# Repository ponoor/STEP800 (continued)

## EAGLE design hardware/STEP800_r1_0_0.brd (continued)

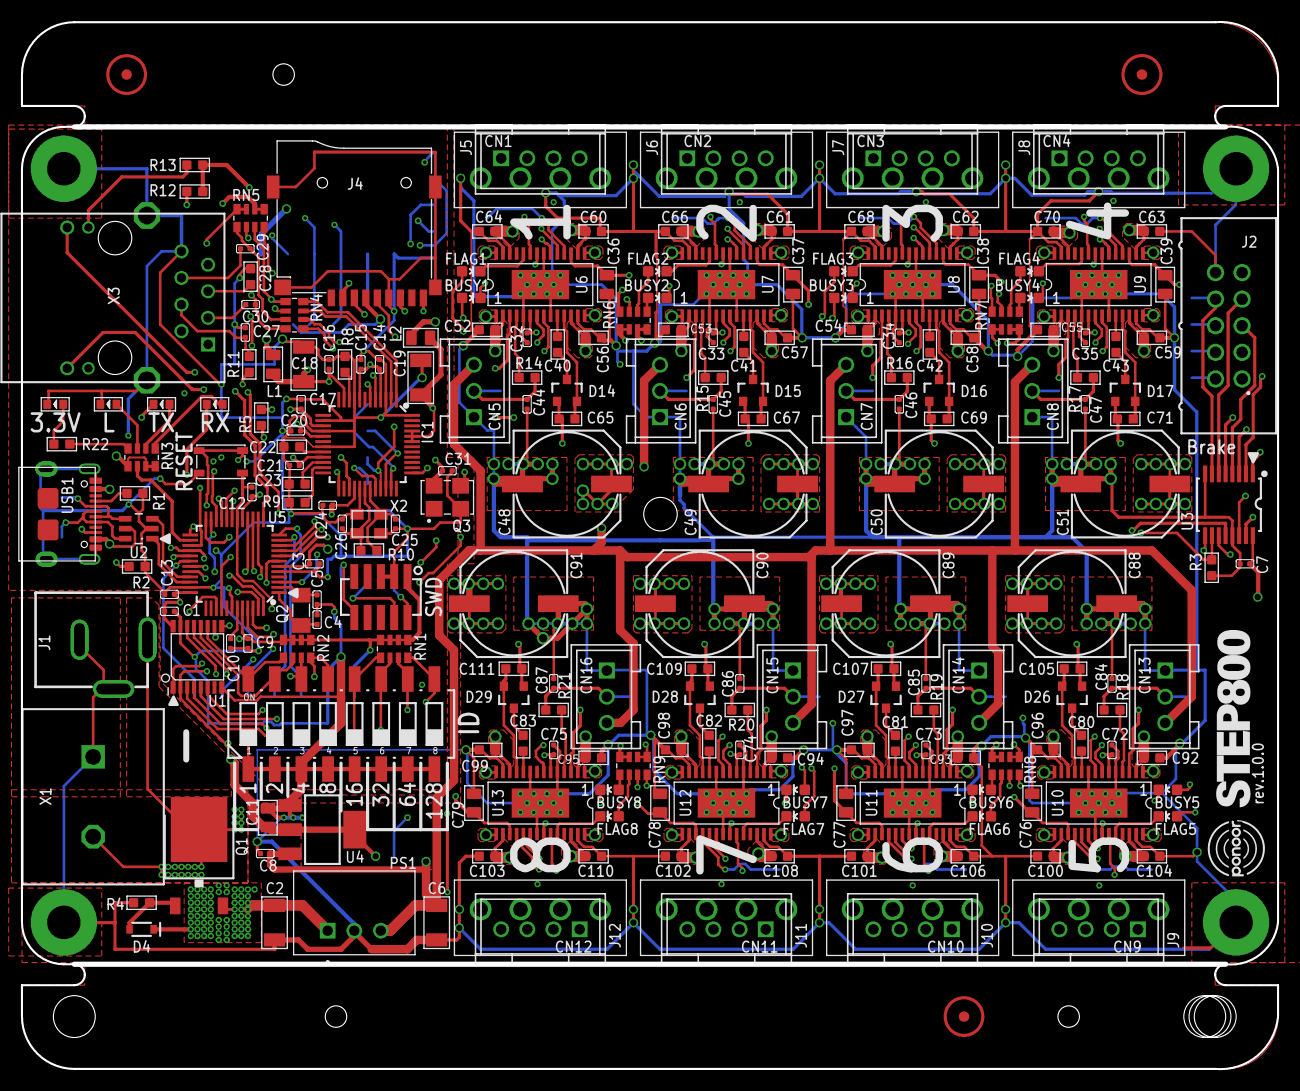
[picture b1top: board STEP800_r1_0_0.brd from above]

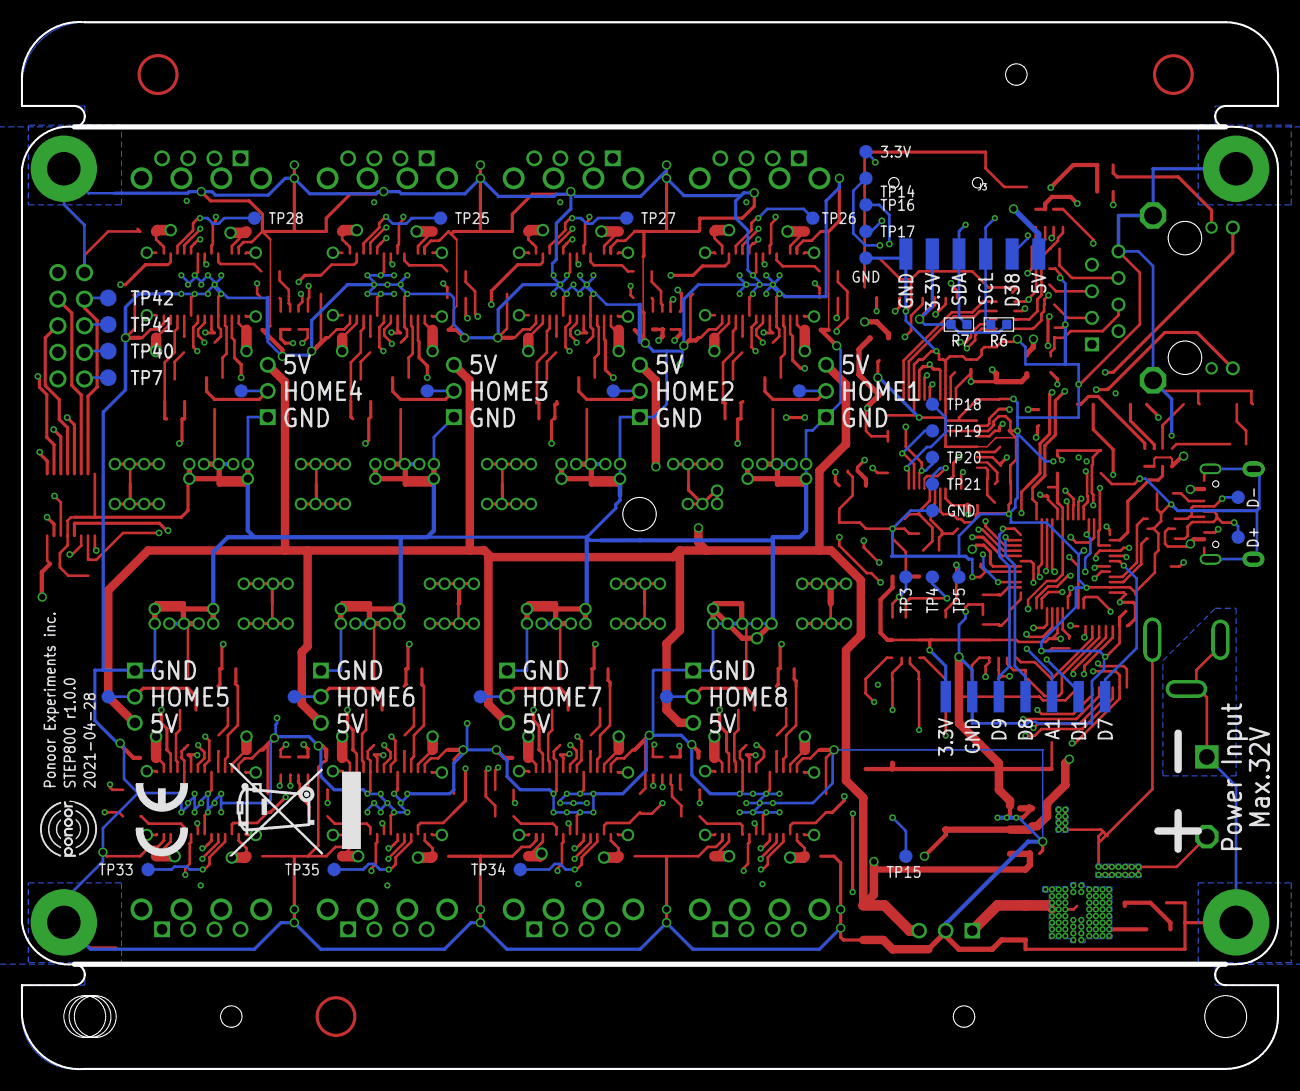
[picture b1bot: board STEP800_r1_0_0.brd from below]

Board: 4 copper layers, 120.0 x 100.0 mm, 280 parts (48 on the bottom side), 219 nets.

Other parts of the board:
U$1: WEEE_13MM
U$2: STEP800_LOGO_L_16MM
U$3: CE_5MM
U$4, U$5: PONOOR_LOGO_6MM

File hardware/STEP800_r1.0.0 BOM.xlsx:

# | Name | Value | Description | Package | Manufacture | MPN | Qty | Parts | Type
1.0 | SMD-LED | GREEN | Various green LEDs | LED-0603 | Everlight Elec | 19-213/GHC-YR1S2M/3T | 9.0 | 3.3V, BUSY1, BUSY2, BUSY3, BUSY4, BUSY5, BUSY6, BUSY7, BUSY8 | SMT
2.0 | MLCC | 100nF / 25V | 100nF / 20% / 25V / X5R | C0402 | Walsin Tech Corp | 0402X104K160CT | 32.0 | C1, C3, C7, C8, C9, C10, C12, C13, C14, C15, C16, C17, C20, C21, C24, C31, C32,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 | SMT
3.0 | MLCC | 10uF/10V | 10uF / 20% / 10V / X5R | C0805 | Samsung Electro-Mechanics | CL21A106KOQNNNG | 9.0 | C11, C36, C37, C38, C39, C76, C77, C78, C79 | SMT
4.0 | MLCC | 47uF/6.3V | 47uF / 20% / 6.3V / X5R | C1206 | Samsung Electro-Mechanics | CL31A476MQHNNWE | 2.0 | C18, C19 | SMT
5.0 | MLCC | 10uF/50V | 10uF / 20% / 50V / X5R | C1206 | Samsung Electro-Mechanics | CL31A106KBHNNNE | 2.0 | C2, C6 | SMT
6.0 | MLCC | 4.7uF / 6.3V | 4.7uF / 20% / 6.3V / X5R | C0603 | Samsung Electro-Mechanics | CL10A475KQ8NNNC | 1.0 | C22 | SMT
7.0 | MLCC | 10nF/50V | 10nF / 20% / 50V / X5R | C0603 | Samsung Electro-Mechanics | CL10B103KB8NNNC | 10.0 | C23, C28, C40, C41, C42, C43, C80, C81, C82, C83 | SMT
8.0 | MLCC | 22nF 50V | 22nF / 20% / 50V / X5R | C0402 | Walsin Tech Corp | 0402F223Z500CT | 1.0 | C27 | SMT
9.0 | MLCC | 6.8nF/25V | 6.8nF / 20% / 25V / X5R | C0402 | Walsin Tech Corp | 0402B682K500CT | 2.0 | C29, C30 | SMT
10.0 | MLCC | 22pF/50V | 22pF / 10% / 50V / X5R | C0402 | Walsin Tech Corp | 0402N220J500 | 4.0 | C4, C5, C25, C26 | SMT
11.0 | MLCC | 220nF / 25V | 220nF / 20% / 25V / X5R | C0603 | Samsung Electro-Mechanics | CL10F224ZA8NNNC | 8.0 | C65, C67, C69, C71, C105, C107, C109, C111 | SMT
12.0 | Chemical Capacitor | 220uF / 50V | 220uF ±20% 50V 10mm | SMD,10x10mm | Rubycon | 50TLV220M10X10.5 | 8.0 | C48, C49, C50, C51, C88, C89, C90, C91 | SMT
13.0 | MLCC | 100nF/50V | 100nF / 20% / 50V / X5R | C0603 | Walsin Tech Corp | 0603B104K500CT | 32.0 | C52, C53, C54, C55, C56, C57, C58, C59, C60, C61, C62, C63, C64, C66, C68, C70,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 | SMT
14.0 | Shrouded header | 2.5mm, 4P | B4B-XASK-1 | B4B-XASK-1 | JST | B04B-XASK-1(LF)(SN) | 8.0 | CN1, CN2, CN3, CN4, CN9, CN10, CN11, CN12 |  | NO MOUNT
15.0 | Shrouded header | 2.5mm, 3P | B3B-XASK-1 | B3B-XASK-1 | JST | B03B-XASK-1(LF)(SN) | 8.0 | CN5, CN6, CN7, CN8, CN13, CN14, CN15, CN16 | THT
16.0 | Switching diode array | BAV99 | Series-pair diode array | SOT23-3 | Nexperia | BAV99,215 | 8.0 | D14, D15, D16, D17, D26, D27, D28, D29 | SMT
17.0 | Zener Diode | 5.6V, 300mW | 5.6V ±7% 300mW | SOD-323 | ON Semiconductor | MM3Z5V6T1G | 1.0 | D4 | SMT
18.0 | SMD-LED | Red | general LED red | LED-0603 | Lite-On | LTST-C193KRKT-5A | 9.0 | FLAG1, FLAG2, FLAG3, FLAG4, FLAG5, FLAG6, FLAG7, FLAG8, TX | SMT
19.0 | Ethernet Controller |  |  | TQFP48 | WIZnet | W5500 | 1.0 | IC1 | SMT
20.0 | DIP Switch |  | 8 digits | 2.54mm pitch SMD | Cixi Tonver Elec | HAD-08HWA-R | 1.0 | ID | SMT
21.0 | DC Power receptacle |  | DC Power Receptacle Jack 5A 2.0mm 6.2mm | POWERJACK_SLOT | XKB Connectivity | DC-005-5A-2.0 | 1.0 | J1 | THT
22.0 | Box header |  | Header 10P 0.100"(2.54mm) 2 | 6.1201021621E10 | BOOMELE(Boom Precision Elec) | C5665 | 1.0 | J2 | THT
23.0 | Micro SD card slot |  |  |  | XUNPU | TF-115K | 1.0 | J4 | SMT
24.0 | 3.81mm 4pin header |  |  |  | Ningbo Kangnex Elec | WJ15EDGVC-3.81-4P | 8.0 | J5, J6, J7, J8, J9, J10, J11, J12 | THT
25.0 | SMD-LED | Orange | general LED orange | LED-0603 | Lite-On | LTST-C191KFKT | 1.0 | L | SMT
26.0 | Ferrite Beads | 330R-1500MA | 330Ω @ 100MHz 1.5A | L0805 | Murata Electronics | BLM21PG331SN1D | 2.0 | L1, L2 | SMT
27.0 | DC-DC Converter | P78E05-1000 | 9-36V input, 5V output, 1000mA | CONV_P78E05-1000 | CUI Inc. | P78E05-1000 | 1.0 | PS1 | THT
28.0 | P-MOSFET |  | 100V 46A | D-PAK(TO252AA) | Winsok Semicon | WSF45P10 | 1.0 | Q1 | SMT
29.0 | Crystal Resonators | 32.768kHz | CRYSTAL | SMD-3215_2P | EPSON | FC-135 32.7680KA-A0 | 1.0 | Q2 | SMT
30.0 | Crystal Oscillator |  | 16MHz ±100ppm 3.3V | SG5032 | Seiko Epson | X1G004451000200 | 1.0 | Q3 | SMT
31.0 | Chip Resistor | 5.1k | ±0.5% 0.1W | R0603 | YAGEO | RC0603DR-075K1L | 2.0 | R1, R2 | SMT
32.0 | Chip Resistor | 1M 1/10W | 5% 1/10W | R0603 | YAGEO | AC0603JR-071ML | 1.0 | R10 | SMT
33.0 | Chip Resistor | 10R | 5% 1/10W | R0603 | YAGEO | RC0603JR-0710RL | 1.0 | R11 | SMT
34.0 | Chip Resistor | 330R | 5% 1/10W | R0603 | YAGEO | RC0603JR-07330RL | 3.0 | R12, R13, R22 | SMT
35.0 | Chip Resistor | 100R | 5% 1/10W | R0603 | YAGEO | RC0603JR-07100RL | 8.0 | R14, R15, R16, R17, R18, R19, R20, R21 | SMT
36.0 | Chip Resistor | 100k | 5% 1/10W | R0603 | YAGEO | RC0603JR-07100KL | 4.0 | R3, R4, R5, R9 | SMT
37.0 | Chip Resistor | 12.4K | 1％ 1/10W | R0603 | YAGEO | AC0603FR-0712K4L | 1.0 | R8 | SMT
38.0 | Tactile Switch |  | SWITCH-SPST | 4.6x3.2 | ALPS Electric | SKRPABE010 | 1.0 | RESET | SMT
39.0 | Array Chip Resistor | 100k | 5% 1/16W | R0603 x4 | Bourns | CAY16-104J4LF | 2.0 | RN1, RN2 | SMT
40.0 | Array Chip Resistor | 330.0 | 5% 1/16W | R0603 x4 | Bourns | CAY16-331J4LF | 5.0 | RN3, RN6, RN7, RN8, RN9 | SMT
41.0 | Array Chip Resistor | 33.0 | 5% 1/16W | R0603 x4 | Bourns | CAY16-330J4LF | 1.0 | RN4 | SMT
42.0 | Array Chip Resistor | 49.9 | 1% 1/16W | R0603 x4 | Bourns | CAY16-49R9F4LF | 1.0 | RN5 | SMT
43.0 | SMD-LED | Yellow | general LED yellow | LED-0603 | Lite-On | LTST-C191KSKT | 1.0 | RX | SMT
44.0 | Pin Header | 10 pin | Cortex Debug Connector | 1.27mm Pin Header 10P | Amphenol ICC | 20021121-00010C4LF | 1.0 | SWD | SMT
45.0 | Logic IC | 74HC165PW | 8-bit parallel-in/serial out shift register | TSSOP16 | Nexperia | 74HC165PW,118 | 1.0 | U1 | SMT
46.0 | TVS Diode Array | USBLC6-2SC6 | STMicroelectronics USBLC6 | SOT23-6L | STMicroelectronics | USBLC6-2SC6 | 1.0 | U2 | SMT
47.0 | Logic IC | 74HC595 | 8-Bit Shift Register (Serial to Parallel) | TSSOP16 | Nexperia | 74HC595PW,118 | 1.0 | U3 | SMT
48.0 | Voltage Regulator | LD1117S33 | 3.3V 0.8A | SOT223 | STMicroelectronics | LD1117S33TR | 1.0 | U4 | SMT
49.0 | MCU |  |  | TQFP-48 | Microchip | ATSAMD21G18A-AU | 1.0 | U5 | SMT
50.0 | Stepper Driver IC |  |  | HTSSOP28 | STMicroelectronics | L6470H | 8.0 | U6, U7, U8, U9, U10, U11, U12, U13 | SMT
51.0 | USB Type C Connector |  | USB - Type C Female 16 SMT | USB-C_USB2.0-TYPE-C | XKB Connectivity | U262-161N-4BVC11 | 1.0 | USB1 | THT
52.0 | Barrier Terminal Block | 7.62mm, 2P |  | 7.62mm | Ningbo Kangnex Elec | WJ25C-B-7.62-2P | 1.0 | X1 | THT
53.0 | Crystal Resonators | 25MHz | 25MHz ±20ppm12pF | CRYSTAL-3225 | Seiko Epson | X1E000021013900 | 1.0 | X2 | SMT
54.0 | RJ45 Jack with Magnetics |  |  |  | Hanrun | HR871181A | 1.0 | X3 | THT

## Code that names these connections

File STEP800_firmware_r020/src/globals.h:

// globals.h

#ifndef _GLOBALS_h
#define _GLOBALS_h

#if defined(ARDUINO) && ARDUINO >= 100
	#include "arduino.h"
#else
	#include "WProgram.h"
#endif
#include <SPI.h>
#include <Ponoor_L6470Library.h>
#include <Ethernet.h>

// =============================================================================
// Board / Pin definitions
// =============================================================================
// #define PROTOTYPE_BLACK // First Black PCB prototype
//#define PROTOTYPE_R3 // Uncomment this line for the prototype r4 pcb.
// r3: revision anno lab 2020
// r4: with brake connector 2021 (production ver)


#ifdef PROTOTYPE_R3 // ----------------- Prototype r3 -----------------
    #define HAS_SD
    #define ledPin	13u
    // L6470
    #define L6470_MISO	6	// D6 /SERCOM3/PAD[2] miso
    #define L6470_MOSI	11	// D11/SERCOM3/PAD[0] mosi
    #define L6470_SCK	12	// D12/SERCOM3/PAD[3] sck

    #define L6470_CS_PIN A0
    #define L6470_RESET_PIN A2
    // Shift registers
    // 74HC165 shift register for dip switch and busy/flag input
    #define MISO3	3 // SERCOM2/PAD[1]
    #define MOSI3   2 // SERCOM2/PAD[2] // not in use
    #define SCK3	0 // SERCOM2/PAD[3]
    #define LATCH3	A5
    // Shift registers SPI
    extern SPIClass SPI3;

    // W5500
    #define W5500_RESET_PIN A3

    #define SETUP_SW_PIN	5u
#elif defined(PROTOTYPE_BLACK) // ----------------- Prototype D_L6470x8_black -----------------
    #define ledPin	4u
    // L6470
    #define L6470_MISO	12	// 
    #define L6470_MOSI	11	// 
    #define L6470_SCK	13	// 
    #define L6470_CS_PIN 9
    #define L6470_RESET_PIN A5
    // Shift Registers
    #define MISO3   A3
    #define LATCH3  A1
    #define SCK3    A2
    // W5500
    #define W5500_RESET_PIN 8
#else // ----------------- Product version -----------------
    #define HAS_SD
    #define HAS_BRAKE
    #define ledPin	13u
    // L6470
    #define L6470_MISO	6	// D6 /SERCOM3/PAD[2] miso
    #define L6470_MOSI	11	// D11/SERCOM3/PAD[0] mosi
    #define L6470_SCK	12	// D12/SERCOM3/PAD[3] sck

    #define L6470_CS_PIN A0
    #define L6470_RESET_PIN A2
    // Shift registers
    // 74HC165 +74HC595 for the dip sw input and the brake output
    #define MISO3	3 // SERCOM2/PAD[1]
    #define MOSI3   2 // SERCOM2/PAD[2]
    #define SCK3	0 // SERCOM2/PAD[3]
    #define LATCH3	A5
    // Shift registers SPI
    extern SPIClass SPI3;

    // W5500
    #define W5500_RESET_PIN A3

    #define SHIFTOUT_ENABLE_PIN 5u
#endif

// =============================================================================
// Pin definitions
// =============================================================================
#ifdef HAS_SD
#define SD_CS_PIN	4u
#define SD_DETECT_PIN   A4
#endif

// =============================================================================
// Constants and variables
// =============================================================================

// General
#define COMPILE_DATE __DATE__
#define COMPILE_TIME __TIME__
extern const char *firmwareName;
extern const uint8_t firmwareVersion[3]; // defined in the main Arduino sketch
extern int8_t loadedConfigVersion[2];
extern const uint8_t applicableConfigVersion[2];
#define STATUS_POLL_PERIOD   1 // [ms]


// Tx, Rx LED
extern bool rxLedEnabled, txLedEnabled;
extern uint32_t RXL_blinkStartTime, TXL_blinkStartTime;
#define RXL_TXL_BLINK_DURATION	30 // ms

// Json configuration file
constexpr char* filename = "/config.txt";
extern String configName;
extern String configTargetProduct;
extern bool sdInitializeSucceeded;
extern bool configFileOpenSucceeded;
extern bool configFileParseSucceeded;

// L6470
#define NUM_OF_MOTOR   (8)
extern AutoDriver stepper[];
#define MOTOR_ID_ALL    255
#define MOTOR_ID_FIRST  1
#define MOTOR_ID_LAST   8

// Network
extern uint8_t mac[6], mac_from_config[6], myId;
extern IPAddress
    myIp,
    myIp_from_config,
    destIp,
    dns,
    gateway,
    subnet;
const IPAddress broadcastIp(255, 255, 255, 255);
extern unsigned int inPort, outPort, outPort_from_config;
extern EthernetUDP Udp;
extern bool
    isDestIpSet,
    isMyIpAddId,
    isMacAddId,
    isOutPortAddId,
    bootedMsgEnable,
    isWaitingSendBootMsg,
    reportErrors;
#define BOOT_MSG_WAIT_TIME  1000    //[ms], The waiting duration for sending a boot message after Ethernet has been linked

// Motor settings.

// Brake
#ifdef HAS_BRAKE
extern uint8_t brakeOut;
#endif
extern uint8_t brakeStatus[NUM_OF_MOTOR];
enum {
    BRAKE_ENGAGED = 0,
    BRAKE_DISENGAGE_WAITING, // motor excited
    BRAKE_DISENGAGED,
    BRAKE_MOTORHIZ_WAITING // brake closed
};
extern uint32_t brakeTransitionTrigTime[NUM_OF_MOTOR];
extern bool bBrakeDecWaiting[NUM_OF_MOTOR]; // Waiting deceleration for the brake engaging procedure

// Homing
extern uint32_t homingStartTime[NUM_OF_MOTOR];
extern uint8_t homingStatus[NUM_OF_MOTOR];
extern bool bHoming[NUM_OF_MOTOR];
extern float homingSpeed[NUM_OF_MOTOR];
enum {
    HOMING_UNDEFINED = 0,
    HOMING_GOUNTIL,
    HOMING_RELEASESW,
    HOMING_COMPLETED,
    HOMING_TIMEOUT
};

// Command errors
enum {
    ERROR_COMMAND_IGNORED = 0,
    ERROR_MOTORID_NOTMATCH,
    ERROR_BRAKE_ENGAGED,
    ERROR_HOMESW_ACTIVATING,
    //ERROR_LIMITSW_ACTIVATING,
    ERROR_GOUNTIL_TIMEOUT,
    ERROR_RELEASESW_TIMEOUT,
    ERROR_IN_SERVO_MODE
};
const String commandErrorText[8] = {
    F("CommandIgnored"),
    F("MotorIdNotMatch"),
    F("BrakeEngaged"),
    F("HomeSwActivating"),
    //F("LimitSwActivating"),
    F("GoUntilTimeout"),
    F("ReleaseSwTimeout"),
    F("InServoMode")
};
// These values will be initialized at loadConfig()
extern bool
    busy[NUM_OF_MOTOR],
    HiZ[NUM_OF_MOTOR],
    homeSwState[NUM_OF_MOTOR],
    dir[NUM_OF_MOTOR],
    uvloStatus[NUM_OF_MOTOR];
extern uint8_t
    motorStatus[NUM_OF_MOTOR],
    thermalStatus[NUM_OF_MOTOR];

extern bool
    reportBUSY[NUM_OF_MOTOR],
    reportHiZ[NUM_OF_MOTOR],
    reportHomeSwStatus[NUM_OF_MOTOR],
    reportDir[NUM_OF_MOTOR],
    reportMotorStatus[NUM_OF_MOTOR],
    reportSwEvn[NUM_OF_MOTOR],
    reportUVLO[NUM_OF_MOTOR],
    reportThermalStatus[NUM_OF_MOTOR],
    reportOCD[NUM_OF_MOTOR],
    reportStall[NUM_OF_MOTOR],
    //limitSwState[NUM_OF_MOTOR],
    //reportLimitSwStatus[NUM_OF_MOTOR],
    //limitSwMode[NUM_OF_MOTOR],
    homingDirection[NUM_OF_MOTOR],
    bProhibitMotionOnHomeSw[NUM_OF_MOTOR],
    //bProhibitMotionOnLimitSw[NUM_OF_MOTOR],
    bHomingAtStartup[NUM_OF_MOTOR];
extern uint16_t
    goUntilTimeout[NUM_OF_MOTOR],
    releaseSwTimeout[NUM_OF_MOTOR];
extern uint8_t kvalHold[NUM_OF_MOTOR], kvalRun[NUM_OF_MOTOR], kvalAcc[NUM_OF_MOTOR], kvalDec[NUM_OF_MOTOR];
//extern uint8_t tvalHold[NUM_OF_MOTOR], tvalRun[NUM_OF_MOTOR], tvalAcc[NUM_OF_MOTOR], tvalDec[NUM_OF_MOTOR];
//extern bool isCurrentMode[NUM_OF_MOTOR];
extern bool homeSwMode[NUM_OF_MOTOR];

extern uint16_t intersectSpeed[NUM_OF_MOTOR]; // INT_SPEED
extern uint8_t
    startSlope[NUM_OF_MOTOR], // ST_SLP
    accFinalSlope[NUM_OF_MOTOR], // FN_SLP_ACC
    decFinalSlope[NUM_OF_MOTOR], // FN_SLP_DEC
    stallThreshold[NUM_OF_MOTOR]; // STALL_TH
// extern uint8_t
//     fastDecaySetting[NUM_OF_MOTOR], // T_FAST
//     minOnTime[NUM_OF_MOTOR], // TON_MIN
//     minOffTime[NUM_OF_MOTOR]; // TOFF_MIN
extern uint8_t
    overCurrentThreshold[NUM_OF_MOTOR], // OCD
    microStepMode[NUM_OF_MOTOR]; // STEP_MODE
extern uint16_t slewRate[NUM_OF_MOTOR]; // GATECFG1
extern uint8_t slewRateNum[NUM_OF_MOTOR]; // [0]114, [1]220, [2]400, [3]520, [4]790, [5]980.
extern float lowSpeedOptimize[NUM_OF_MOTOR];
extern bool electromagnetBrakeEnable[NUM_OF_MOTOR];
extern uint16_t brakeTransitionDuration[NUM_OF_MOTOR];
extern float
    acc[NUM_OF_MOTOR],
    dec[NUM_OF_MOTOR],
    maxSpeed[NUM_OF_MOTOR],
    fullStepSpeed[NUM_OF_MOTOR];

// Servo mode
extern int32_t targetPosition[NUM_OF_MOTOR];
extern float kP[NUM_OF_MOTOR], kI[NUM_OF_MOTOR], kD[NUM_OF_MOTOR];
extern boolean isServoMode[NUM_OF_MOTOR];
#endif

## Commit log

2021-04-14 Added hardware design files
2021-04-20 Added firmware files
2021-04-23 Added multiple boards support
2021-04-27 Fixed a SPI pin for shift registers
2021-04-28 Fixed loading myIp, outPort and mac when the DIP sw changed.
    And PROTOTYPE_BLACK bugs fix
2021-04-28 Updated the diagnosis outputs
2021-04-28 Updated hardware design files
2021-04-30 Fixed the L6470 reset pin logic state for prototype pcb
2021-05-03 Fixed the wrong parsing when loading integer as bool in the config.txt
2021-05-07 Silk adjustments for the Eagle board design file
2021-05-09 Added the hardware inspection sketch
2021-05-10 Updated the hardware test sketch
2021-05-17 Correct the external OSC frequency for prototype_black
2021-07-12 Rename test_prcedure.md to 1_preparation.md
2021-07-16 update the hardware test sketch
2021-08-30 configTools item name typo fixed
    goUntilTimeout
2021-08-30 configTool html+js update
2021-08-31 changed the directory name for the firmware
2021-09-01 changed a structure of directories
2021-09-03 Fixed the diagnosis tool serial output problem
2021-09-03 added hardware dimension files
2021-09-03 Fixed a usb serial output problem of the diagnosis tool
2021-09-05 config tool css+html update
2021-09-08 configTools CSS
2021-09-13 led test sketch
2021-09-14 led test sketch update
2021-10-18 Added configProductApplicable
2021-10-18 Update Arduino sketch folder
2021-11-25 Added minSpeed commands for the firmware and the config tool.
2021-11-25 added getMinSpeed command
2021-12-02 added /resetDeive and remove /resetDev
2021-12-08 added position report commands, update setElPos arguments
2021-12-08 updated Arduino sketch folder
2022-01-14 fixed `/getLowSpeedOptimizeThreshold` response bug.
2022-01-19 Fixed the thermal status return value
2022-02-13 check the homing status for motion/stop commands
2022-02-14 only `/run` can interrupt a homing among motion commands
    Other motion commands will be ignored during a homing.
2022-03-03 Fixed the incorrect `/getHomeSw` response.
2022-03-24 added the link to the latest firmware
2023-03-10 generate the brake board schematic
2023-03-10 generate the board layout
2023-03-17 brake board pcb design update
2023-04-05 brake conv gerber data for the prototype
2023-09-09 hardware test sketch update to adapt new SAMD SPI function name
2023-09-10 The hardware test sketch updated
    Added LED tests.
2024-03-03 typo
